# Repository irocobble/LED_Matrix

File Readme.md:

# STM32 8×8 LED Matrix Driver

**Team Name:** ?

## AIM
To design a custom PCB that drives an 8×8 LED matrix (64 LEDs) using an 
STM32F103C8T6 microcontroller, using transistor-based multiplexing instead 
of a dedicated LED driver IC — and to use it as a stepping stone for 
learning custom STM32 PCB design end-to-end (schematic, layout, fab, bring-up).

---

## Design Path — What We Tried First

The first version of the schematic used MMBT2222A (NPN) transistors for 
both the row and column drivers. This works fine for the rows, which sink 
current to GND — a standard common-emitter low-side switch. It does not 
work cleanly for the columns, which are high-side switches: the transistor 
emitter sits at +3.3V, and the GPIO has to pull the base *above* the 
emitter to turn an NPN on, which it can't do from the same 3.3V rail. 
Fixed by switching the column drivers to MMBT2907A (PNP), where the GPIO 
pulls the base low relative to the 3.3V emitter instead.

The 3.3V regulator (LM1117MP-ADJ) needs a feedback resistor divider on the 
ADJ pin to set its output voltage — this should be confirmed present in 
the final schematic, or the part swapped for the fixed-output LM1117-3.3.

Both crystals (Y1: 12MHz for CH340G, Y2: 8MHz for STM32) are passive, with 
load capacitors and series resistors on each. Load cap values were 
recalculated based on the actual crystal's datasheet rated load 
capacitance (12pF for the YXC YSX321SL used on the CH340G side) rather 
than left at a generic default.

---

## How It Works — The Big Picture

**USB-C (5V)** → **LM1117 regulator** → **STM32F103C8T6** → **GPIO row/column scan** → **BJT drivers** → **8×8 LED matrix**

The MCU drives one row low and one column high at a time, cycling through 
all 8×8 = 64 LEDs fast enough that persistence of vision makes the whole 
matrix appear continuously lit. Only one LED is physically on at any instant.

Separately, **USB-C** → **CH340G** → **UART (PA9/PA10)** lets the board be 
programmed and debugged over the same USB-C connector, using the STM32's 
built-in UART bootloader — no ST-Link required.

---

## Key Definitions

* **Row/Column Multiplexing:** Driving a 2D LED grid with only 16 GPIO 
  (8 rows + 8 columns) instead of 64, by lighting one row/column intersection 
  at a time and relying on persistence of vision.
* **High-side / Low-side Switching:** A low-side switch sits between the 
  load and GND (sinks current); a high-side switch sits between the supply 
  and the load (sources current). NPN BJTs suit low-side switching off the 
  same rail as the GPIO; PNP BJTs suit high-side switching, for the same 
  reason in reverse.
* **Load Capacitor (Crystal):** A capacitor placed on each leg of a passive 
  crystal to bring the circuit's effective capacitance to the value the 
  crystal was designed to oscillate at (its rated load capacitance).
* **Ground/Power Plane:** A dedicated PCB layer filled with copper tied to 
  GND or a supply rail, used for low-impedance return paths and easier 
  routing on a multi-layer board.
* **Via Stitching:** Vias placed to connect copper pours on different 
  layers (e.g. multiple GND fills), improving return-current paths and 
  thermal spreading.
* **UART Bootloader:** A factory-programmed ROM bootloader on STM32 parts 
  that allows flashing firmware over UART (instead of SWD/JTAG) when BOOT0 
  is pulled high at reset.
* **ESD Protection Diode:** A component that clamps voltage transients on a 
  signal line (e.g. USB D+/D-) to protect downstream ICs from static discharge.
* **Polyfuse:** A resettable fuse that increases resistance under overcurrent 
  and resets automatically once the fault clears, unlike a one-time fuse.

---

## Hardware

* **MCU:** STM32F103C8T6 — ARM Cortex-M3, 72 MHz, 64 KB Flash, 20 KB SRAM
* **Display:** 8×8 LED matrix (64 LEDs), each column gated through its own 
  current-limiting resistor (R13–R20)
* **Matrix Drivers:** 16 × SOT-23 BJTs — 8× MMBT2907A (PNP, column high-side), 
  8× MMBT2222A (NPN, row low-side)
* **Power Input:** USB-C, 5V
* **Regulation:** LM1117MP-ADJ — feedback divider to be confirmed before fab
* **USB-UART Bridge:** CH340G with 12 MHz passive crystal (YXC YSX321SL, 12pF load cap)
* **System Clock:** 8 MHz passive crystal on STM32
* **Programming:** UART bootloader via BOOT0 selection, no ST-Link required
* **Protection:** USB-C CC resistors, polyfuse, ESD diodes, ferrite bead on VBUS
* **Controls:** Reset and BOOT0 push buttons

| Module | Component |
|---|---|
| MCU | STM32F103C8T6 |
| Column drivers (high-side) | 8 × MMBT2907A (PNP, SOT-23) |
| Row drivers (low-side) | 8 × MMBT2222A (NPN, SOT-23) |
| LED current limiting | R13–R20 (per-column resistors) |
| USB-UART bridge | CH340G + 12 MHz crystal |
| Regulator | LM1117MP-ADJ |
| System oscillator | 8 MHz crystal |
| USB connector | USB-C receptacle |

**Design tool:** KiCad 9.0.3

**Source files:** [link to your repo]

---

## PCB Layout

* **Board size:** 35×35mm
* **Layer count:** 4 layers
  * L1 (top): Signal routing
  * L2: GND plane
  * L3: 3.3V plane
  * L4 (bottom): Signal routing
* Power and ground as solid internal planes gives low-impedance return 
  paths for the digital signals on the outer layers and simplifies routing 
  density around the STM32 and LED matrix.

---

## Firmware — Planned Approach

* MCU scans rows/columns using a timer interrupt for consistent refresh rate
* Frame buffer in SRAM holds the current 8×8 bitmap; the scan routine only 
  reads from it, so updating the display is just writing to the buffer
* Brightness control planned via Bit Angle Modulation (BAM) for per-LED 
  grayscale, layered on top of the row/column scan — no hardware change 
  required, this is a firmware-only addition
* UART bootloader flow: pull BOOT0 high, reset, flash via STM32CubeProgrammer, 
  pull BOOT0 low, reset again to run

---

## Repository Structure

```text
├── Hardware/
│   ├── Schematic
│   ├── PCB Layout
│   └── Manufacturing Files
├── Firmware/
│   ├── Source Code
│   └── Build Files
└── Documentation/
```

---

## Current Status

* [x] Schematic — PNP columns, per-LED current-limiting resistors, passive crystals
* [x] Confirm LM1117MP-ADJ feedback divider is present and correctly valued
* [x] PCB routing — first pass complete, 4-layer stackup
* [x] Run DRC and confirm zero unrouted nets / clearance violations
* [ ] Prototype fabrication
* [ ] Hardware validation
* [ ] Firmware development
* [ ] Display animation library (brightness/BAM, frame buffer, basic patterns)

---

## Limitations and Future Work

The LM1117MP-ADJ regulator's feedback divider needs to be confirmed on the 
final schematic before fabrication. A few possible unrouted nets/airwires 
were visible on the top copper layer near the crystal and BJT driver area 
during review — DRC should be run to confirm full routing before sending 
to fab. No explicit ground-stitching vias were added near the row-driver 
BJT cluster, which sinks up to ~160mA when a full row is lit; this is not 
a blocker but could improve return-current path and thermal performance. 
The design uses discrete BJTs for all 16 drivers instead of a dedicated 
LED matrix driver IC (e.g. MAX7219), which is simpler to wire but uses more 
board space and GPIO pins than a driver-IC approach. Brightness control 
(PWM/BAM dimming) is planned but not yet implemented in firmware.

## License

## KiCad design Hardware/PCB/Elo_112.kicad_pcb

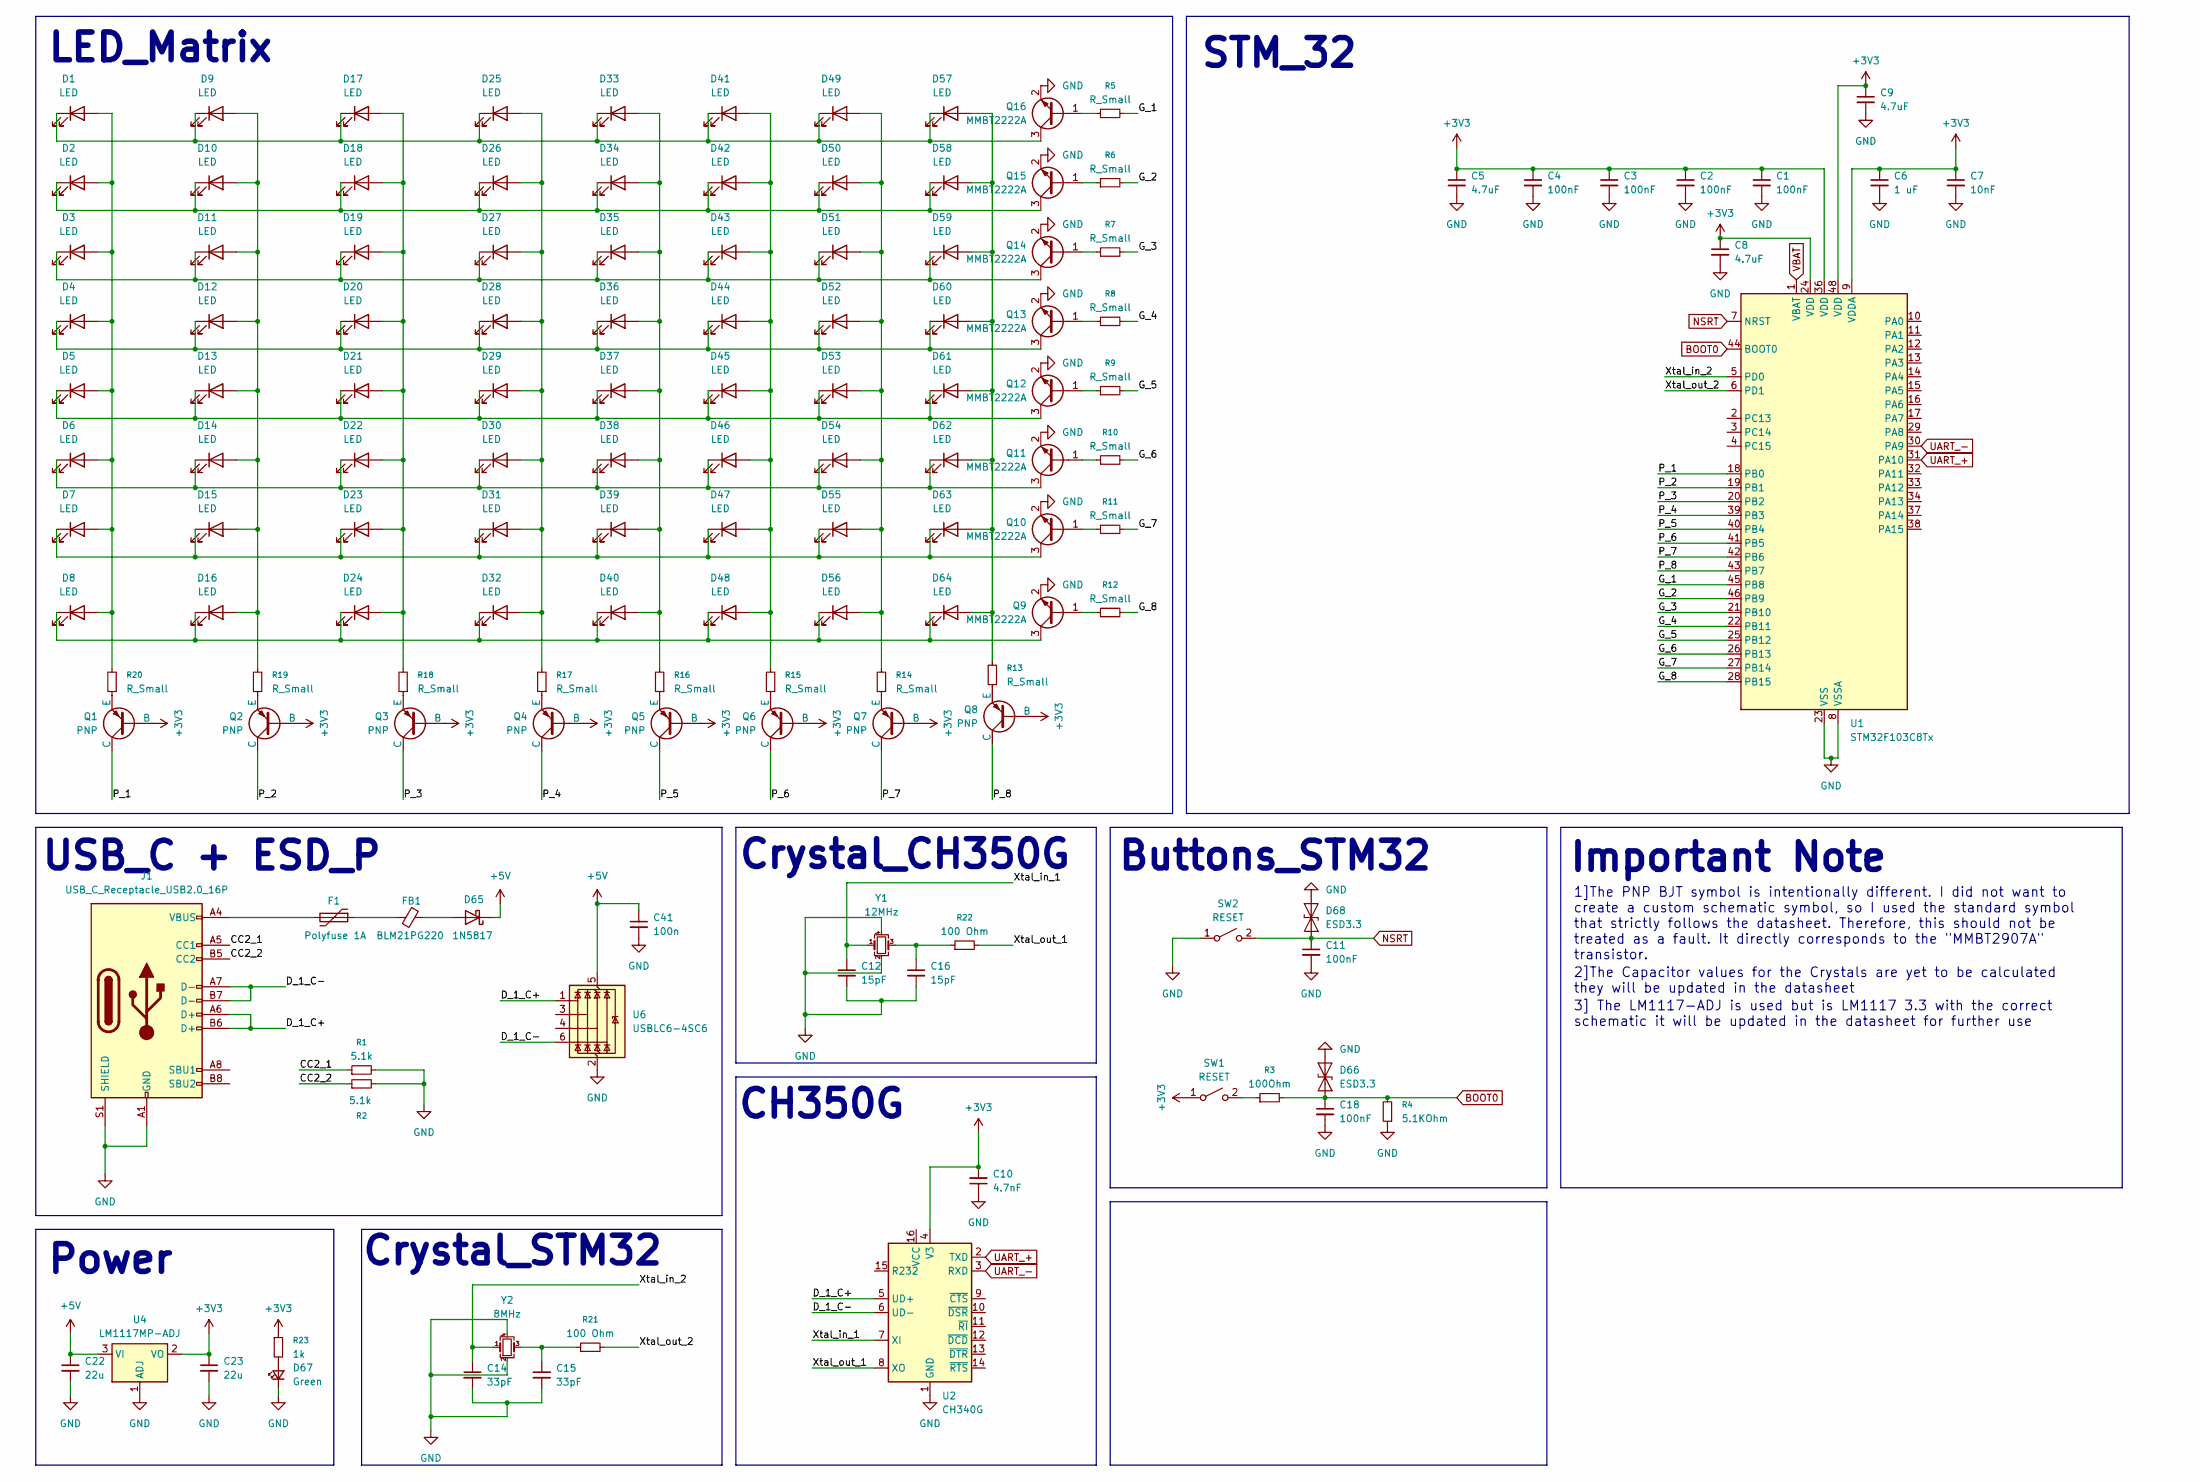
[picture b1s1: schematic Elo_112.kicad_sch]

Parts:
C1, C2, C3, C4, C11, C18: 100nF; C_0402_1005Metric
C5, C8, C9: 4.7uF; C_0402_1005Metric
C6: 1 uF; C_0402_1005Metric
C7: 10nF; C_0402_1005Metric
C10: 4.7nF; C_0402_1005Metric
C12, C16: 15pF; C_0402_1005Metric
C14, C15: 33pF; C_0402_1005Metric
C22, C23: 22u; C_0402_1005Metric
C41: 100n; C_0402_1005Metric
D1, D2, D3, D4, D5, D6, D7, D8, D9, D10, D11, D12, D13, D14, D15, D16, D17, D18, D19, D20, D21, D22, D23, D24, D25, D26, D27, D28, D29, D30, D31, D32, D33, D34, D35, D36, D37, D38, D39, D40, D41, D42, D43, D44, D45, D46, D47, D48, D49, D50, D51, D52, D53, D54, D55, D56, D57, D58, D59, D60, D61, D62, D63, D64: LED; LED_0402_1005Metric
D65: 1N5817; D_SOD-123
D66, D68: ESD3.3; SODFL1006X40N
D67: Green; LED_0805_2012Metric
F1: Polyfuse 1A; FUSC1608X100N
FB1: BLM21PG220; IND_BLM21_MUR-L
J1: USB_C_Receptacle_USB2.0_16P; USB_C_Receptacle_HCTL_HC-TYPE-C-16P-01A
Q1, Q2, Q3, Q4, Q5, Q6, Q7, Q8: PNP; SOT-23
Q9, Q10, Q11, Q12, Q13, Q14, Q15, Q16: MMBT2222A; SOT-23
R1, R2: 5.1k; R_0402_1005Metric
R3: 100Ohm; R_0402_1005Metric
R4: 5.1KOhm; R_0402_1005Metric
R5, R6, R7, R8, R9, R10, R11, R12, R13, R14, R15, R16, R17, R18, R19, R20: R_Small; R_0402_1005Metric
R21, R22: 100 Ohm; R_0402_1005Metric
R23: 1k; R_0402_1005Metric
SW1, SW2: RESET; SW_CS1213AGF260_CRS
U1: STM32F103C8Tx; LQFP-48_7x7mm_P0.5mm
U2: CH340G; SOIC-16_3.9x9.9mm_P1.27mm
U4: LM1117MP-ADJ; DCY0004A_L
U6: USBLC6-4SC6; SOT-23-6
Y1: 12MHz; Crystal_SMD_3225-4Pin_3.2x2.5mm
Y2: 8MHz; Crystal_SMD_3225-4Pin_3.2x2.5mm

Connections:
+3V3: C1.1, C2.1, C3.1, C4.1, C5.1, C6.1, C7.1, C8.1, C9.1, C10.2, C23.1, Q1.2 (B), Q2.2 (B), Q3.2 (B), Q4.2 (B), Q5.2 (B), Q6.2 (B), Q7.2 (B), Q8.2 (B), R23.1, SW1.1 (A), U1.9 (VDDA), U1.24 (VDD), U1.36 (VDD), U1.48 (VDD), U2.4 (V3), U4.2 (VO)
+5V: C22.1, C41.1, D65.1 (K), U4.3 (VI), U6.5 (VBUS)
/CC2_1: J1.A5 (CC1), R1.1
/CC2_2: J1.B5 (CC2), R2.1
/D_1_C+: J1.A6 (D+), J1.B6 (D+), U2.5 (UD+), U6.1 (I/O1)
/D_1_C-: J1.A7 (D-), J1.B7 (D-), U2.6 (UD-), U6.6 (I/O4)
/G_1: R5.2, U1.45 (PB8)
/G_2: R6.2, U1.46 (PB9)
/G_3: R7.2, U1.21 (PB10)
/G_4: R8.2, U1.22 (PB11)
/G_5: R9.2, U1.25 (PB12)
/G_6: R10.2, U1.26 (PB13)
/G_7: R11.2, U1.27 (PB14)
/G_8: R12.2, U1.28 (PB15)
/P_1: Q1.1 (C), U1.18 (PB0)
/P_2: Q2.1 (C), U1.19 (PB1)
/P_3: Q3.1 (C), U1.20 (PB2)
/P_4: Q4.1 (C), U1.39 (PB3)
/P_5: Q5.1 (C), U1.40 (PB4)
/P_6: Q6.1 (C), U1.41 (PB5)
/P_7: Q7.1 (C), U1.42 (PB6)
/P_8: Q8.1 (C), U1.43 (PB7)
/Xtal_in_1: C12.1, U2.7 (XI), Y1.1
/Xtal_in_2: C14.1, U1.5 (PD0), Y2.1
/Xtal_out_1: R22.2, U2.8 (XO)
/Xtal_out_2: R21.2, U1.6 (PD1)
BOOT0: C18.1, D66.1 (A1), R3.2, R4.2, U1.44 (BOOT0)
GND: C1.2, C2.2, C3.2, C4.2, C5.2, C6.2, C7.2, C8.2, C9.2, C10.1, C11.2, C12.2, C14.2, C15.2, C16.2, C18.2, C22.2, C23.2, C41.2, D66.2 (A2), D67.1 (K), D68.2 (A2), J1.A1 (GND), J1.A12 (GND), J1.B1 (GND), J1.B12 (GND), J1.S1 (SHIELD), Q9.2 (E), Q10.2 (E), Q11.2 (E), Q12.2 (E), Q13.2 (E), Q14.2 (E), Q15.2 (E), Q16.2 (E), R1.2, R2.2, R4.1, SW2.1 (A), U1.8 (VSSA), U1.23 (VSS), U1.35 (VSS), U1.47 (VSS), U2.1 (GND), U4.1 (ADJ), U6.2 (GND), Y1.2, Y1.4, Y2.2, Y2.4
NSRT: C11.1, D68.1 (A1), SW2.2 (B), U1.7 (NRST)
unnamed: C15.1, R21.1, Y2.3
unnamed: C16.1, R22.1, Y1.3
unnamed: D1.2 (A), D2.2 (A), D3.2 (A), D4.2 (A), D5.2 (A), D6.2 (A), D7.2 (A), D8.2 (A), R20.2
unnamed: D1.1 (K), D9.1 (K), D17.1 (K), D25.1 (K), D33.1 (K), D41.1 (K), D49.1 (K), D57.1 (K), Q16.3 (C)
unnamed: D9.2 (A), D10.2 (A), D11.2 (A), D12.2 (A), D13.2 (A), D14.2 (A), D15.2 (A), D16.2 (A), R19.2
unnamed: D2.1 (K), D10.1 (K), D18.1 (K), D26.1 (K), D34.1 (K), D42.1 (K), D50.1 (K), D58.1 (K), Q15.3 (C)
unnamed: D3.1 (K), D11.1 (K), D19.1 (K), D27.1 (K), D35.1 (K), D43.1 (K), D51.1 (K), D59.1 (K), Q14.3 (C)
unnamed: D4.1 (K), D12.1 (K), D20.1 (K), D28.1 (K), D36.1 (K), D44.1 (K), D52.1 (K), D60.1 (K), Q13.3 (C)
unnamed: D5.1 (K), D13.1 (K), D21.1 (K), D29.1 (K), D37.1 (K), D45.1 (K), D53.1 (K), D61.1 (K), Q12.3 (C)
unnamed: D6.1 (K), D14.1 (K), D22.1 (K), D30.1 (K), D38.1 (K), D46.1 (K), D54.1 (K), D62.1 (K), Q11.3 (C)
unnamed: D7.1 (K), D15.1 (K), D23.1 (K), D31.1 (K), D39.1 (K), D47.1 (K), D55.1 (K), D63.1 (K), Q10.3 (C)
unnamed: D8.1 (K), D16.1 (K), D24.1 (K), D32.1 (K), D40.1 (K), D48.1 (K), D56.1 (K), D64.1 (K), Q9.3 (C)
unnamed: D17.2 (A), D18.2 (A), D19.2 (A), D20.2 (A), D21.2 (A), D22.2 (A), D23.2 (A), D24.2 (A), R18.2
unnamed: D25.2 (A), D26.2 (A), D27.2 (A), D28.2 (A), D29.2 (A), D30.2 (A), D31.2 (A), D32.2 (A), R17.2
unnamed: D33.2 (A), D34.2 (A), D35.2 (A), D36.2 (A), D37.2 (A), D38.2 (A), D39.2 (A), D40.2 (A), R16.2
unnamed: D41.2 (A), D42.2 (A), D43.2 (A), D44.2 (A), D45.2 (A), D46.2 (A), D47.2 (A), D48.2 (A), R15.2
unnamed: D49.2 (A), D50.2 (A), D51.2 (A), D52.2 (A), D53.2 (A), D54.2 (A), D55.2 (A), D56.2 (A), R14.2
unnamed: D57.2 (A), D58.2 (A), D59.2 (A), D60.2 (A), D61.2 (A), D62.2 (A), D63.2 (A), D64.2 (A), R13.2
unnamed: D65.2 (A), FB1.1
unnamed: D67.2 (A), R23.2
unnamed: F1.1, FB1.2
unnamed: F1.2, J1.A4 (VBUS), J1.A9 (VBUS), J1.B4 (VBUS), J1.B9 (VBUS)
unnamed: Q1.3 (E), R20.1
unnamed: Q2.3 (E), R19.1
unnamed: Q3.3 (E), R18.1
unnamed: Q4.3 (E), R17.1
unnamed: Q5.3 (E), R16.1
unnamed: Q6.3 (E), R15.1
unnamed: Q7.3 (E), R14.1
unnamed: Q8.3 (E), R13.1
unnamed: Q9.1 (B), R12.1
unnamed: Q10.1 (B), R11.1
unnamed: Q11.1 (B), R10.1
unnamed: Q12.1 (B), R9.1
unnamed: Q13.1 (B), R8.1
unnamed: Q14.1 (B), R7.1
unnamed: Q15.1 (B), R6.1
unnamed: Q16.1 (B), R5.1
unnamed: R3.1, SW1.2 (B)
UART_+: U1.31 (PA10), U2.2 (TXD)
UART_-: U1.30 (PA9), U2.3 (RXD)
VBAT: U1.1 (VBAT)

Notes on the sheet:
2]The Capacitor values for the Crystals are yet to be calculated they will be updated in the datasheet
3] The LM1117-ADJ is used but is LM1117 3.3 with the correct schematic it will be updated in the datasheet for further use
Buttons_STM32
1]The PNP BJT symbol is intentionally different. I did not want to create a custom schematic symbol, so I used the standard symbol that strictly follows the datasheet. Therefore, this should not be treated as a fault. It directly corresponds to the "MMBT2907A" transistor.
USB_C + ESD_P
Crystal_STM32
CH350G
Power
Crystal_CH350G
STM_32
LED_Matrix
Important Note

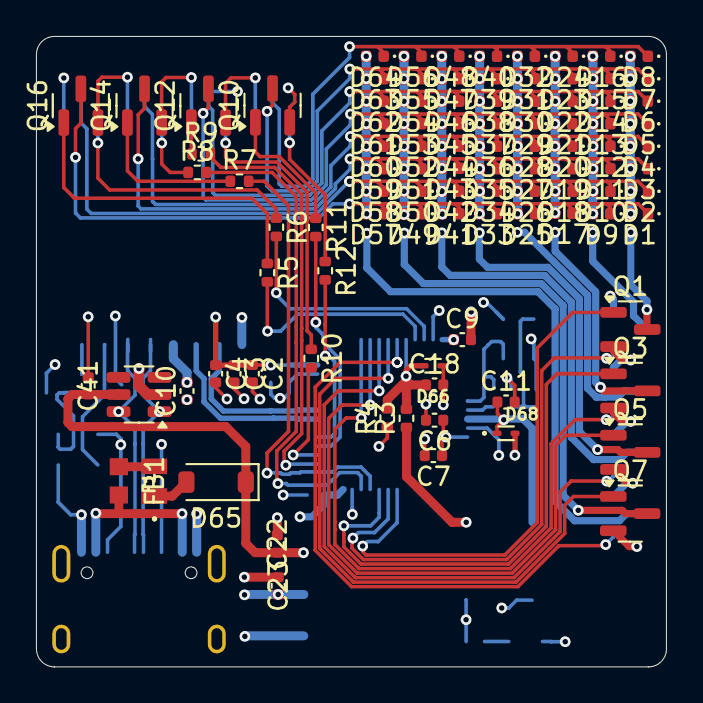
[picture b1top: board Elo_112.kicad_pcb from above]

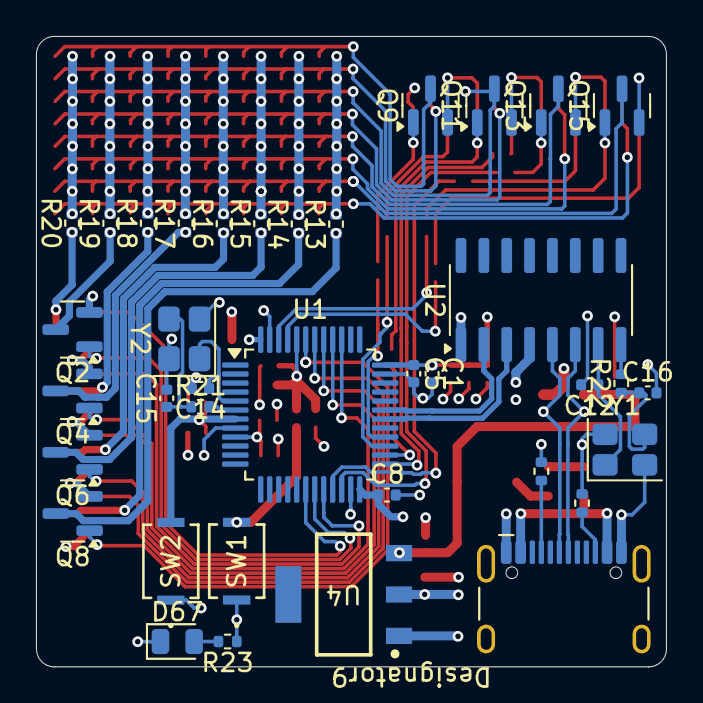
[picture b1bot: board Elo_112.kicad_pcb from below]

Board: 4 copper layers, 35.0 x 35.0 mm, 137 parts (37 on the bottom side), 70 nets.

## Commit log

2026-06-29 updated the schematics
2026-06-29 Deleted dublicate files
2026-06-29 Deleted duble dir
2026-06-30 Updated Readme to have the PCB routing content.md
